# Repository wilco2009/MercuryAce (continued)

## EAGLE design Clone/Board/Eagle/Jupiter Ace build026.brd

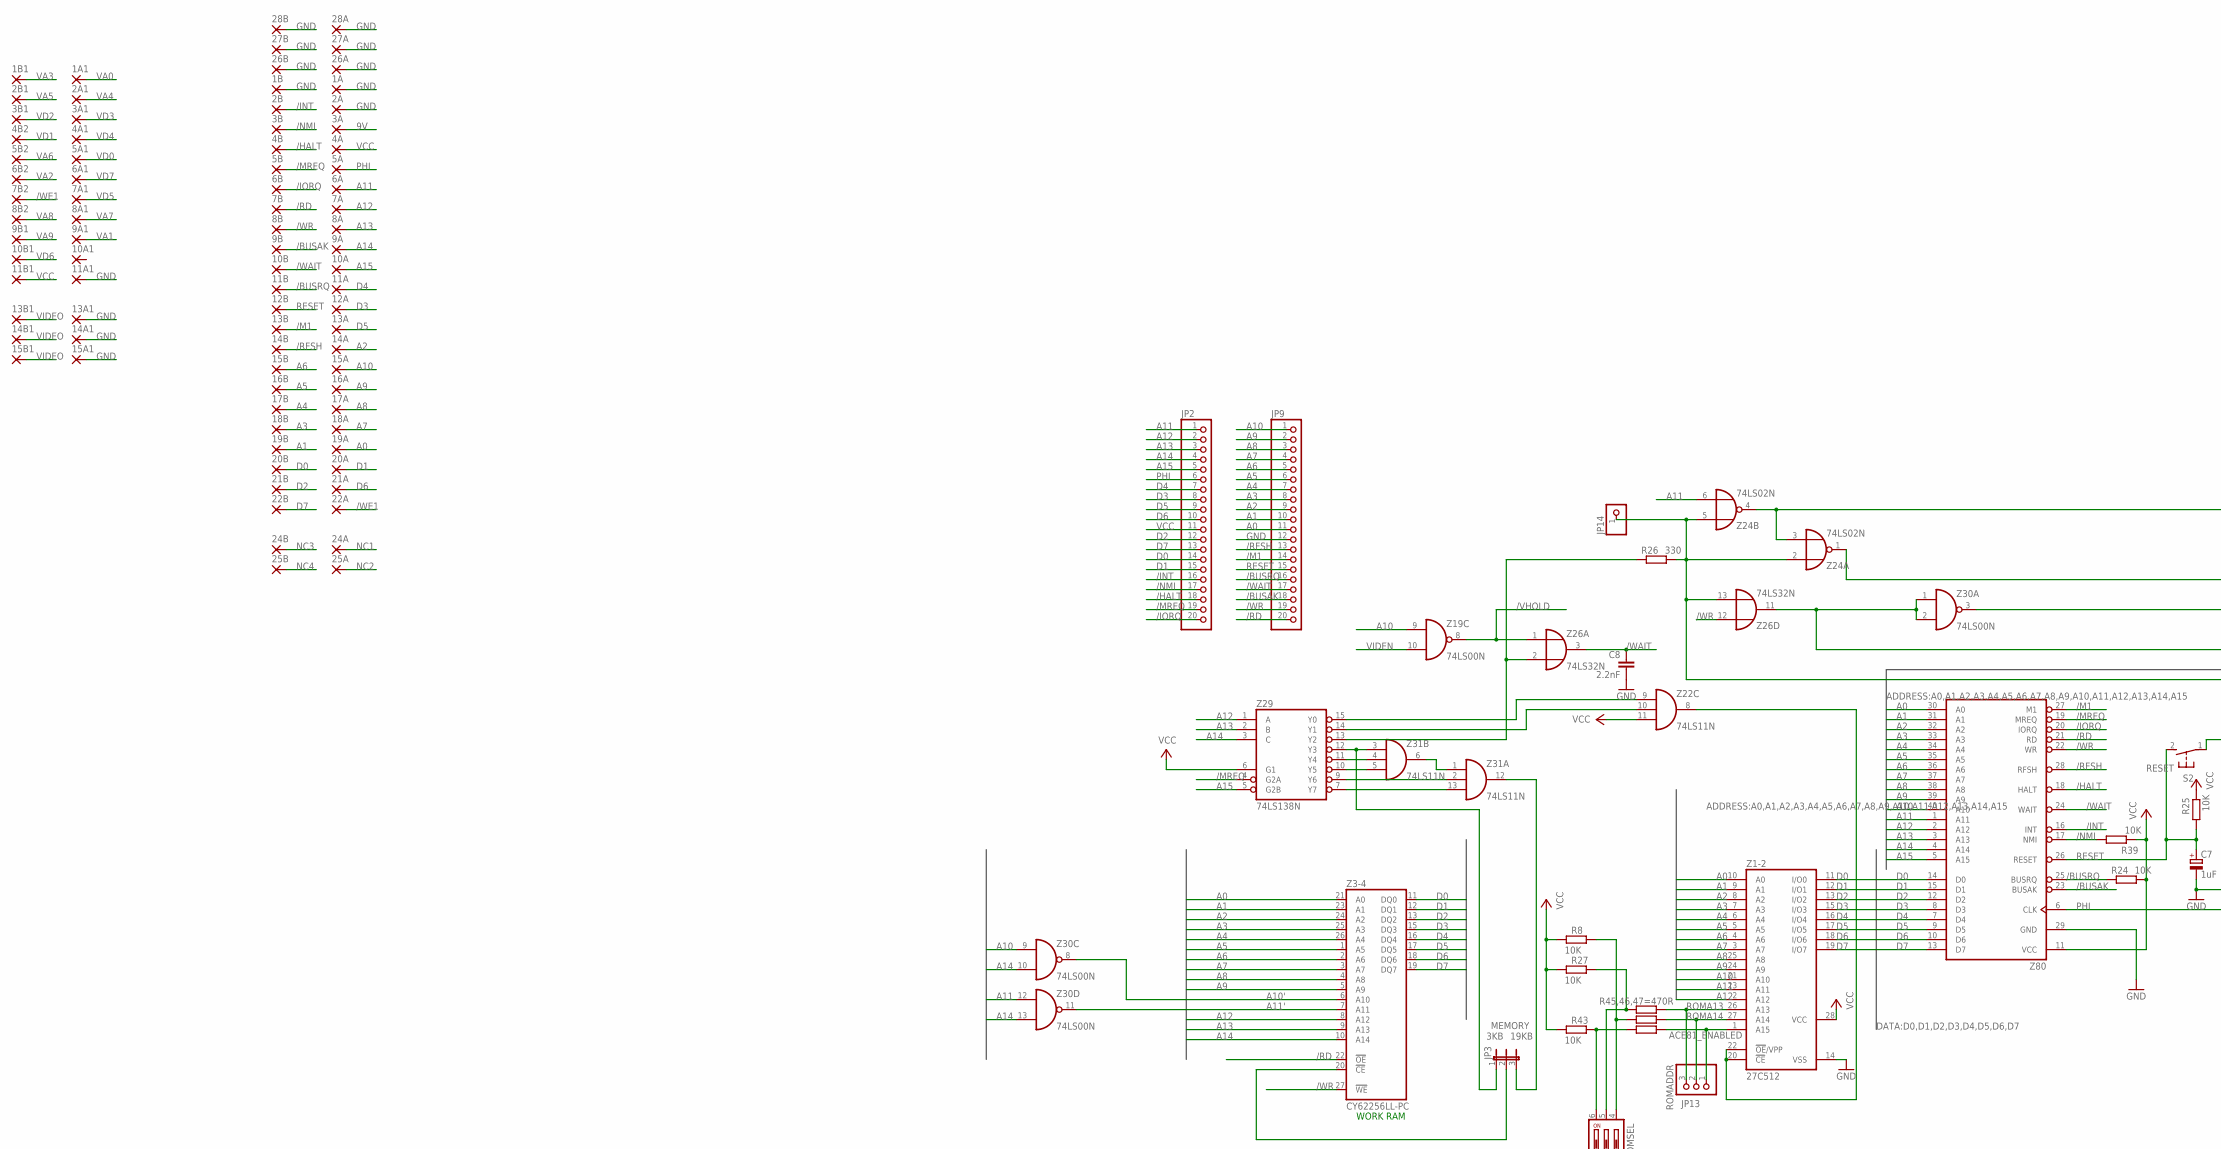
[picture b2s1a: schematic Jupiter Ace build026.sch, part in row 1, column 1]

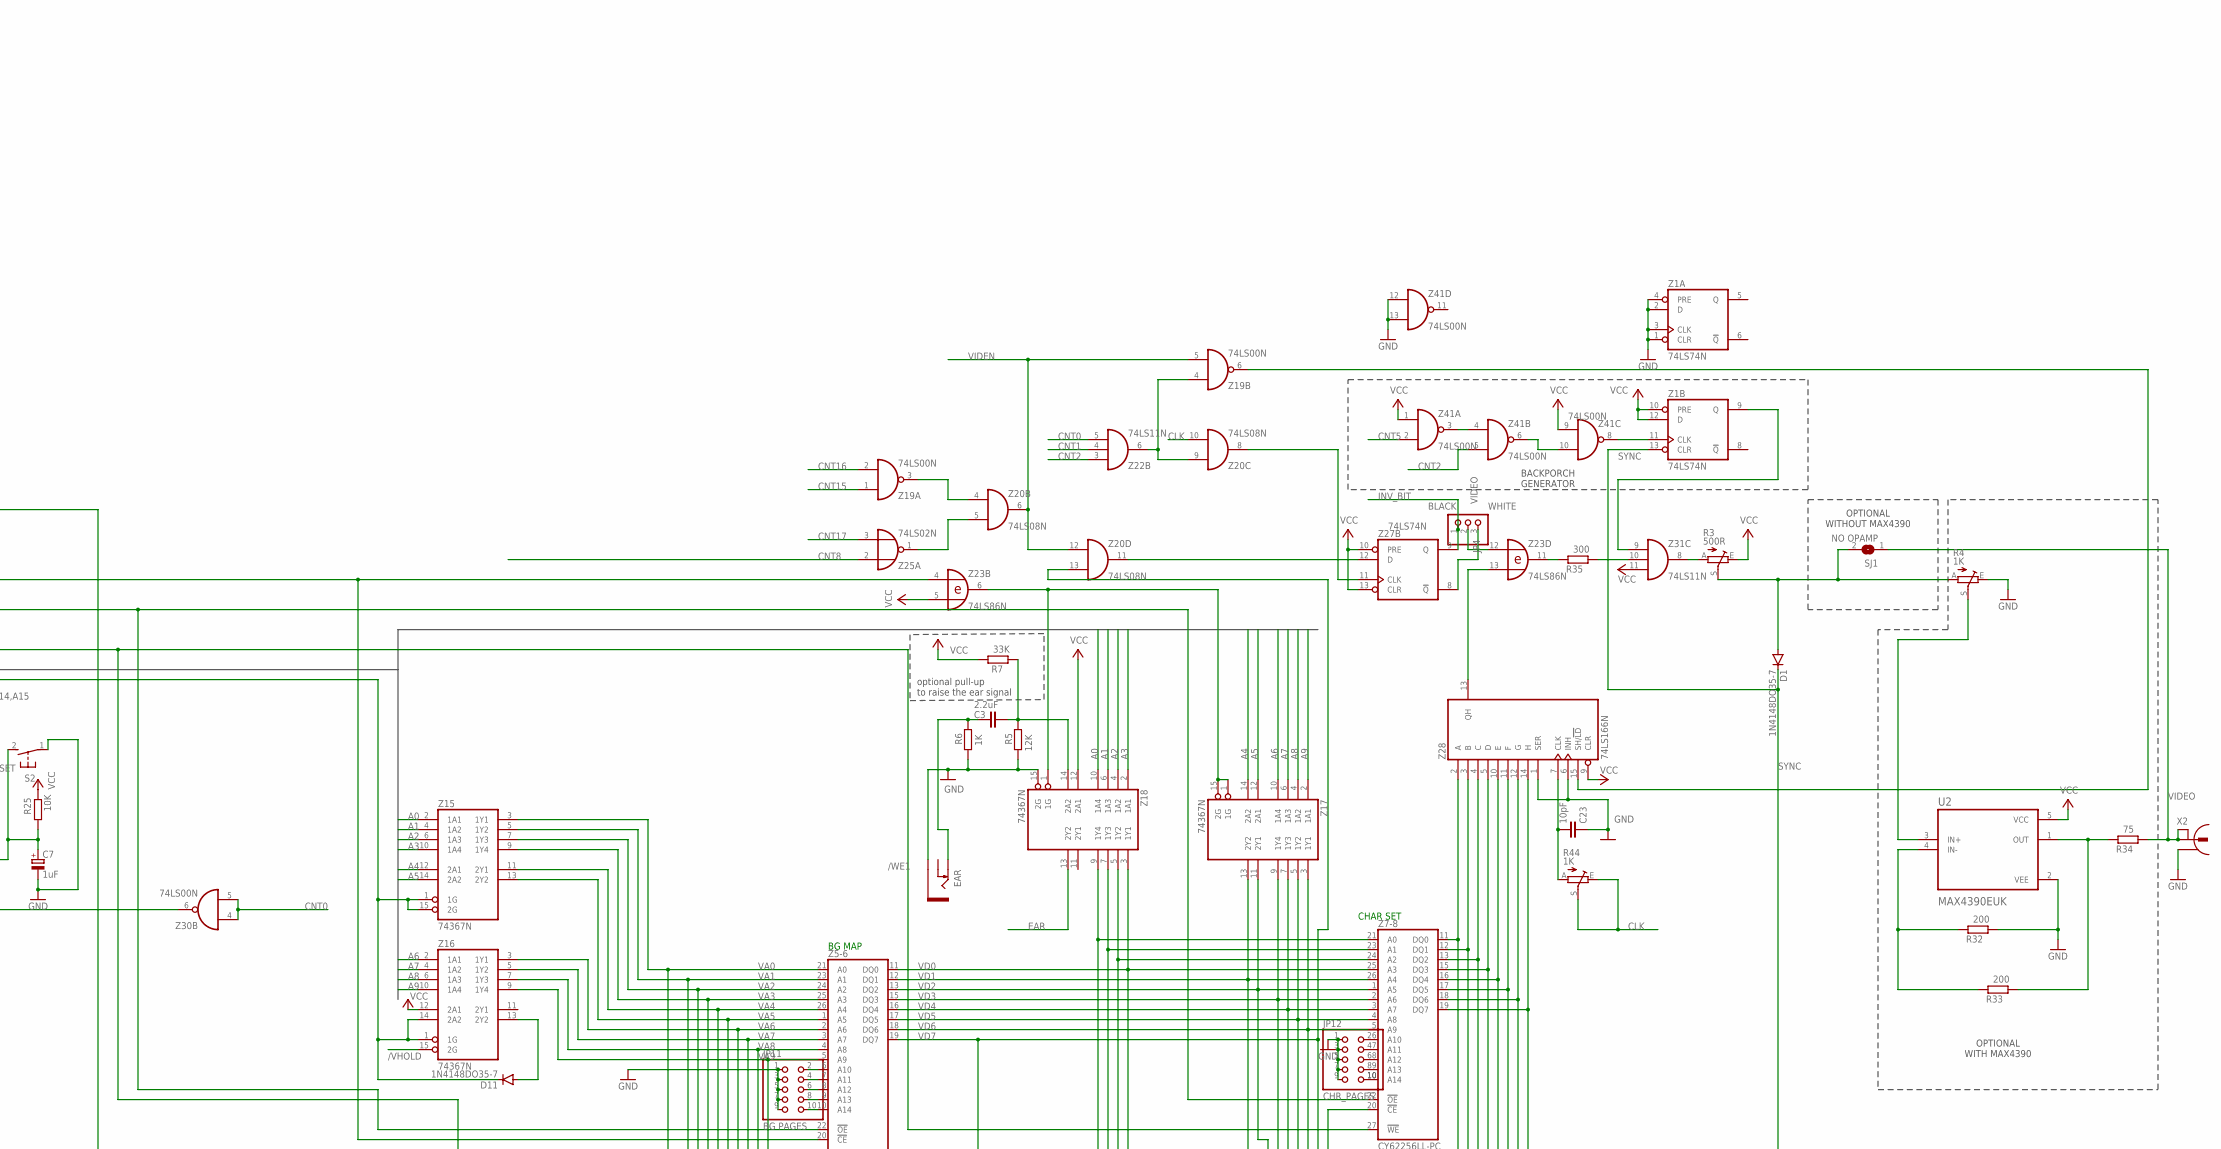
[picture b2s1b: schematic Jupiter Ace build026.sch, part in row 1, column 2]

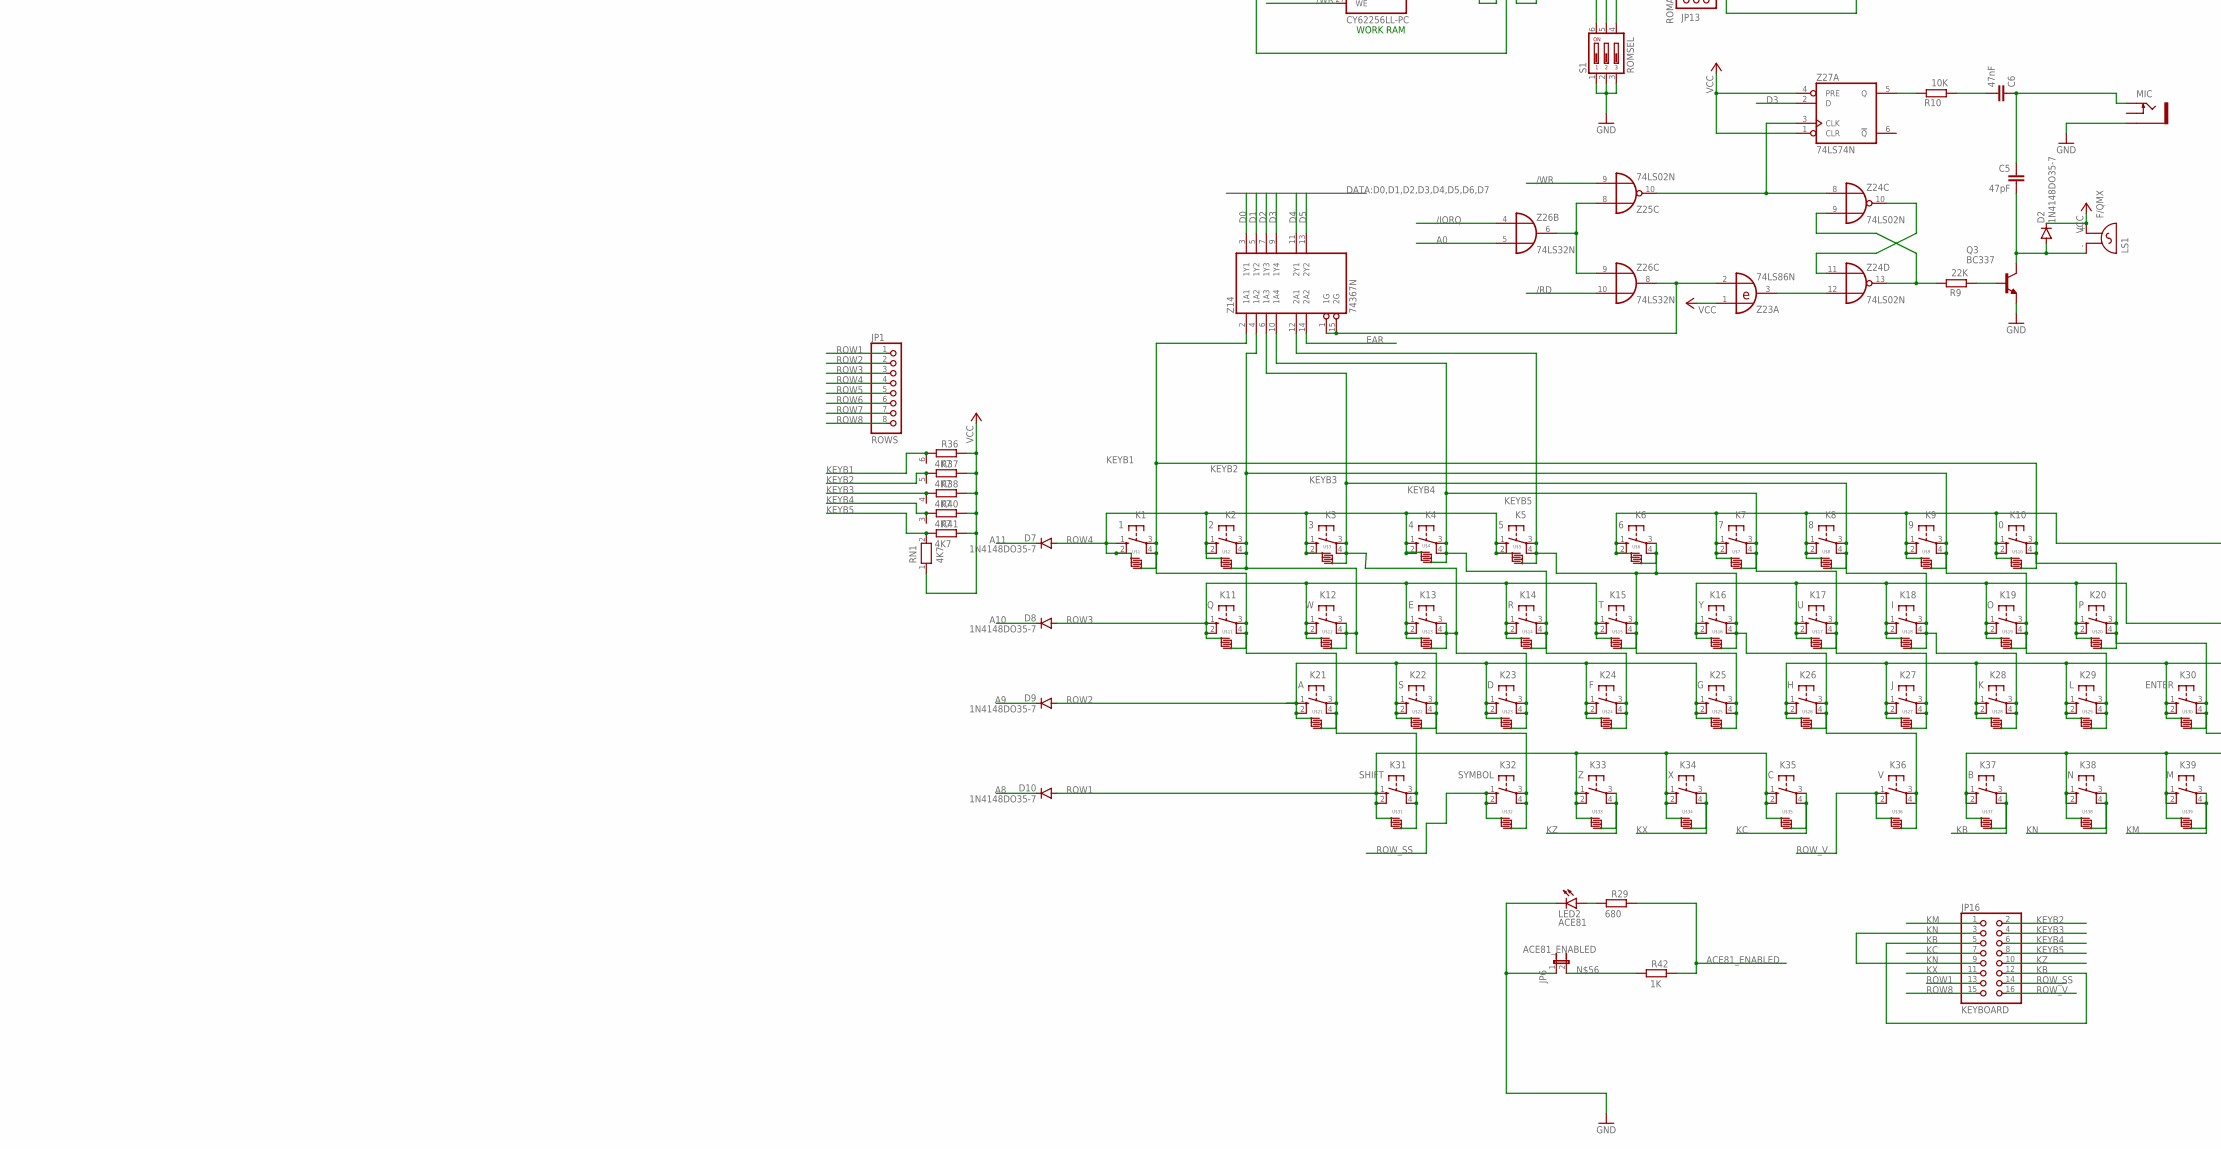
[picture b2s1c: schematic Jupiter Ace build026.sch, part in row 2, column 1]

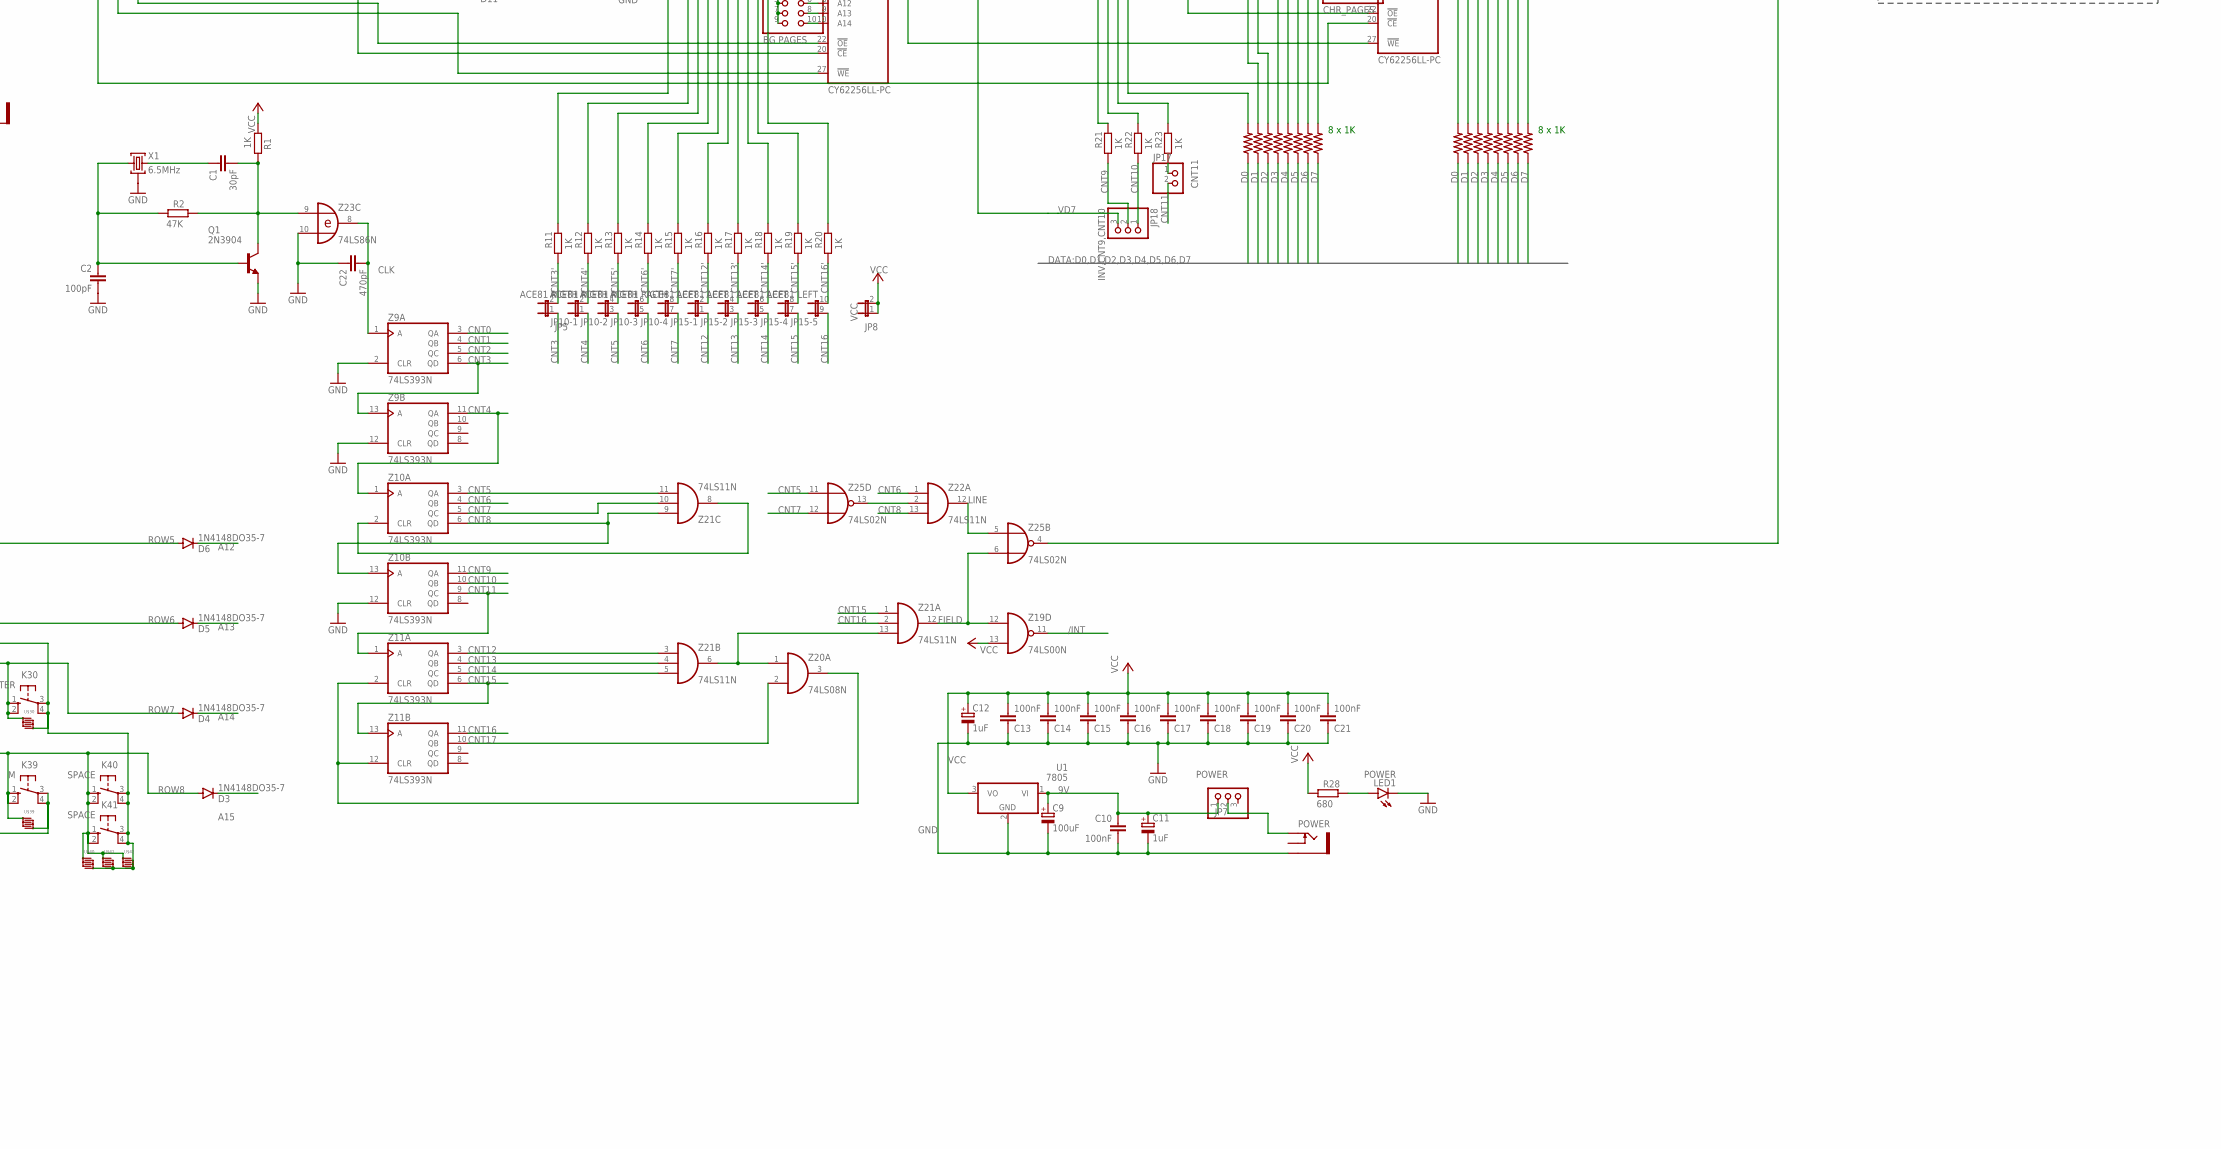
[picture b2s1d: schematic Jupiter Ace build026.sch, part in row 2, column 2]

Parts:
1A, 1A1, 1B, 1B1, 2A, 2A1, 2B, 2B1, 3A, 3A1, 3B, 3B1, 4A, 4A1, 4B, 4B2, 5A, 5A1, 5B, 5B2, 6A, 6A1, 6B, 6B2, 7A, 7A1, 7B, 7B2, 8A, 8A1, 8B, 8B2, 9A, 9A1, 9B, 9B1, 10A, 10A1, 10B, 10B1, 11A, 11A1, 11B, 11B1, 12A, 12B, 13A, 13A1, 13B, 13B1, 14A, 14A1, 14B, 14B1, 15A, 15A1, 15B, 15B1, 16A, 16B, 17A, 17B, 18A, 18B, 19A, 19B, 20A, 20B, 21A, 21B, 22A, 22B, 24A, 24B, 25A, 25B, 26A, 26B, 27A, 27B, 28A, 28B: SMD2EDGEPIN; EDGEPIN
C1: 30pF; C025-025X050
C2: 100pF; C025-025X050
C3: 2.2uF; C025-025X050
C5: 47pF; C025-025X050
C6: 47nF; C025-025X050
C7, C11, C12: 1uF; E1,8-4
C8: 2.2nF; C025-025X050
C9: 100uF; E1,8-4
C10, C13, C14, C15, C16, C17, C18, C19, C20, C21: 100nF; C025-025X050
C22: 470pF; C025-025X050
C23: 10pF; C025-025X050
D1, D2, D3, D4, D5, D6, D7, D8, D9, D10, D11: 1N4148DO35-7; DO35-7
EAR: PJ302M
JP1: ROWS; 1X08
JP2, JP9: PINHD-1X20; 1X20
JP3: MEMORY; JP2
JP4: VIDEO; 1X03
JP5: JP1E1Q; JP1Q
JP6: ACE81_ENABLED; JP1Q
JP7: POWER; 1X03
JP8: VCC; JP1Q
JP10: ACE81 RIGTH; JP4Q
JP11: BG PAGES; 2X05
JP12: CHR_PAGES; 2X05
JP13: ROMADDR; 1X03
JP14: PINHD-1X1; 1X01
JP15: ACE81 LEFT; JP5Q
JP16: KEYBOARD; 2X08
JP17: CNT11; 1X02
JP18: INV,CNT9,CNT10; 1X03
K1: 1; B3F-40XXNOHOLE
K2: 2; B3F-40XXNOHOLE
K3: 3; B3F-40XXNOHOLE
K4: 4; B3F-40XXNOHOLE
K5: 5; B3F-40XXNOHOLE
K6: 6; B3F-40XXNOHOLE
K7: 7; B3F-40XXNOHOLE
K8: 8; B3F-40XXNOHOLE
K9: 9; B3F-40XXNOHOLE
K10: 0; B3F-40XXNOHOLE
K11: Q; B3F-40XXNOHOLE
K12: W; B3F-40XXNOHOLE
K13: E; B3F-40XXNOHOLE
K14: R; B3F-40XXNOHOLE
K15: T; B3F-40XXNOHOLE
K16: Y; B3F-40XXNOHOLE
K17: U; B3F-40XXNOHOLE
K18: I; B3F-40XXNOHOLE
K19: O; B3F-40XXNOHOLE
K20: P; B3F-40XXNOHOLE
K21: A; B3F-40XXNOHOLE
K22: S; B3F-40XXNOHOLE
K23: D; B3F-40XXNOHOLE
K24: F; B3F-40XXNOHOLE
K25: G; B3F-40XXNOHOLE
K26: H; B3F-40XXNOHOLE
K27: J; B3F-40XXNOHOLE
K28: K; B3F-40XXNOHOLE
K29: L; B3F-40XXNOHOLE
K30: ENTER; B3F-40XXNOHOLE
K31: SHIFT; B3F-40XXNOHOLE
K32: SYMBOL; B3F-40XXNOHOLE
K33: Z; B3F-40XXNOHOLE
K34: X; B3F-40XXNOHOLE
K35: C; B3F-40XXNOHOLE
K36: V; B3F-40XXNOHOLE
K37: B; B3F-40XXNOHOLE
K38: N; B3F-40XXNOHOLE
K39: M; B3F-40XXNOHOLE
K40, K41: SPACE; B3F-40XXNOHOLE
LED1: POWER; LED3MM
LED2: ACE81; LED3MM
LS1: F/QMX
MIC: PJ302M
POWER: PJ302M
Q1: 2N3904; TO92
Q3: BC337; TO92
R1, R6, R11, R12, R13, R14, R15, R16, R17, R18, R19, R20, R42: 1K; 0204/7
R2: 47K; 0204/7
R3: 500R; B25P
R4, R44: 1K; B25P
R5: 12K; 0204/7
R7: 33K; 0204/7
R8, R10, R24, R25, R27, R39, R43: 10K; 0204/7
R9: 22K; 0204/7
R21, R22, R23, R100, R101, R102, R103, R104, R105, R106, R107, R200, R201, R202, R203, R204, R205, R206, R207: 1K; 0204V
R26: 330; 0204/7
R28, R29: 680; 0204/7
R32, R33: 200; 0204/7
R34: 75; 0204/7
R35: 300; 0204/7
R36, R37, R38, R40, R41: 4K7; 0207/10
R45, R46, R47: 470R; 0204/7
RN1: 4K7; RN-6
S1: ROMSEL; DP-03
S2: RESET; B3F-31XX
SJ1: NO OPAMP; SJ
U1: 7805; TO220V
U2: MAX4390EUK; SOT95P280X145-5N
U$1, U$2, U$3, U$4, U$5, U$6, U$7, U$8, U$9, U$10, U$11, U$12, U$13, U$14, U$15, U$16, U$17, U$18, U$19, U$20, U$21, U$22, U$23, U$24, U$25, U$26, U$27, U$28, U$29, U$30, U$31, U$32, U$33, U$34, U$35, U$36, U$37, U$38, U$39, U$40, U$41, U$42: 40-XX-CARBON; CARBONB3F
X1: 6.5MHz; HC49U
X2: CON-CONRAD_736880-49
Z0: Z80; DIL40
Z1, Z27: 74LS74N; DIL14
Z1-2: 27C512; DIL28-6
Z3-4, Z5-6, Z7-8: CY62256LL-PC; DIL28-6
Z9, Z10, Z11: 74LS393N; DIL14
Z14, Z15, Z16, Z17, Z18: 74367N; DIL16
Z19, Z30, Z41: 74LS00N; DIL14
Z20: 74LS08N; DIL14
Z21, Z22, Z31: 74LS11N; DIL14
Z23: 74LS86N; DIL14
Z24, Z25: 74LS02N; DIL14
Z26: 74LS32N; DIL14
Z28: 74LS166N; DIL16
Z29: 74LS138N; DIL16

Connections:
9V: 3A.1, C9.+, C10.1, C11.+, JP7.1, U1.1 (VI)
/BUSAK: 9B.1, JP9.18, Z0.23 (BUSAK)
/BUSRQ: 11B.1, JP9.16, R24.1, Z0.25 (BUSRQ)
/HALT: 4B.1, JP2.18, Z0.18 (HALT)
/INT: 2B.1, JP2.16, Z0.16 (INT), Z19.11 (O)
/IORQ: 6B.1, JP2.20, Z0.20 (IORQ), Z26.4 (I0)
/M1: 13B.1, JP9.14, Z0.27 (M1)
/MREQ: 5B.1, JP2.19, Z0.19 (MREQ), Z29.4 (G2A)
/NMI: 3B.1, JP2.17, R39.1, Z0.17 (NMI)
/RD: 7B.1, JP9.20, Z0.21 (RD), Z3-4.22 (!OE), Z26.10 (I1)
/RFSH: 14B.1, JP9.13, Z0.28 (RFSH)
/VHOLD: Z16.15 (2G), Z19.8 (O), Z26.1 (I0)
/WAIT: 10B.1, C8.1, JP9.17, Z0.24 (WAIT), Z26.3 (O)
/WE1: 7B2.1, 22A.1, Z5-6.27 (!WE), Z7-8.27 (!WE), Z26.11 (O), Z30.1 (I0), Z30.2 (I1)
/WR: 8B.1, JP9.19, Z0.22 (WR), Z3-4.27 (!WE), Z25.9 (I1), Z26.12 (I0)
A0: 19A.1, JP9.11, Z0.30 (A0), Z1-2.10 (A0), Z3-4.21 (A0), Z15.2 (1A1), Z18.10 (1A4), Z26.5 (I1)
A1: 19B.1, JP9.10, Z0.31 (A1), Z1-2.9 (A1), Z3-4.23 (A1), Z15.4 (1A2), Z18.6 (1A3)
A2: 14A.1, JP9.9, Z0.32 (A2), Z1-2.8 (A2), Z3-4.24 (A2), Z15.6 (1A3), Z18.4 (1A2)
A3: 18B.1, JP9.8, Z0.33 (A3), Z1-2.7 (A3), Z3-4.25 (A3), Z15.10 (1A4), Z18.2 (1A1)
A4: 17B.1, JP9.7, Z0.34 (A4), Z1-2.6 (A4), Z3-4.26 (A4), Z15.12 (2A1), Z17.14 (2A2)
A5: 16B.1, JP9.6, Z0.35 (A5), Z1-2.5 (A5), Z3-4.1 (A5), Z15.14 (2A2), Z17.12 (2A1)
A6: 15B.1, JP9.5, Z0.36 (A6), Z1-2.4 (A6), Z3-4.2 (A6), Z16.2 (1A1), Z17.10 (1A4)
A7: 18A.1, JP9.4, Z0.37 (A7), Z1-2.3 (A7), Z3-4.3 (A7), Z16.4 (1A2), Z17.6 (1A3)
A8: 17A.1, D10.C, JP9.3, Z0.38 (A8), Z1-2.25 (A8), Z3-4.4 (A8), Z16.6 (1A3), Z17.4 (1A2)
A9: 16A.1, D9.C, JP9.2, Z0.39 (A9), Z1-2.24 (A9), Z3-4.5 (A9), Z16.10 (1A4), Z17.2 (1A1)
A10: 15A.1, D8.C, JP9.1, Z0.40 (A10), Z1-2.21 (A10), Z19.9 (I0), Z30.9 (I0)
A10': Z3-4.6 (A10), Z30.8 (O)
A11: 6A.1, D7.C, JP2.1, Z0.1 (A11), Z1-2.23 (A11), Z24.6 (I1), Z30.12 (I0)
A11': Z3-4.7 (A11), Z30.11 (O)
A12: 7A.1, D6.C, JP2.2, Z0.2 (A12), Z1-2.2 (A12), Z3-4.8 (A12), Z29.1 (A)
A13: 8A.1, D5.C, JP2.3, Z0.3 (A13), Z3-4.9 (A13), Z29.2 (B)
A14: 9A.1, D4.C, JP2.4, Z0.4 (A14), Z3-4.10 (A14), Z29.3 (C), Z30.10 (I1), Z30.13 (I1)
A15: 10A.1, D3.C, JP2.5, Z0.5 (A15), Z29.5 (G2B)
ACE81_ENABLED: JP13.1, R29.2, R42.2, R47.2, Z1-2.1 (A15)
AMPLIF_IN: R4.S, U2.3 (IN+)
AMPLIF_OUT: R33.1, R34.2, U2.1 (OUT)
CLK: C22.2, R44.E, R44.S, Z9.1 (A), Z20.10 (I1), Z23.8 (O)
CNT0: Z9.3 (QA), Z22.5 (I2), Z30.4 (I0), Z30.5 (I1)
CNT1: Z9.4 (QB), Z22.4 (I1)
CNT2: Z9.5 (QC), Z22.3 (I0), Z41.5 (I1)
CNT3: JP5.1, Z9.6 (QD), Z9.13 (A)
CNT3': JP5.2, R11.1
CNT4: JP10.1, Z9.11 (QA), Z10.1 (A)
CNT4': JP10.2, R12.1
CNT5: JP10.3 (1), Z10.3 (QA), Z21.11 (I2), Z25.11 (I0), Z41.2 (I1)
CNT5': JP10.4 (2), R13.1
CNT6: JP10.5 (1), Z10.4 (QB), Z22.1 (I0)
CNT6': JP10.6 (2), R14.1
CNT7: JP10.7 (1), Z10.5 (QC), Z21.10 (I1), Z25.12 (I1)
CNT7': JP10.8 (2), R15.1
CNT8: Z10.6 (QD), Z10.13 (A), Z21.9 (I0), Z22.13 (I2), Z25.2 (I0)
CNT9: JP18.2, R21.1, Z10.11 (QA)
CNT10: JP18.1, R22.1, Z10.10 (QB)
CNT11: JP17.2, Z10.9 (QC), Z11.1 (A)
CNT12: JP15.1, Z11.3 (QA), Z21.3 (I0)
CNT12': JP15.2, R16.1
CNT13: JP15.3 (1), Z11.4 (QB), Z21.4 (I1)
CNT13': JP15.4 (2), R17.1
CNT14: JP15.5 (1), Z11.5 (QC), Z21.5 (I2)
CNT14': JP15.6 (2), R18.1
CNT15: JP15.7 (1), Z11.6 (QD), Z11.13 (A), Z19.1 (I0), Z21.1 (I0)
CNT15': JP15.8 (2), R19.1
CNT16: JP15.9 (1), Z11.11 (QA), Z19.2 (I1), Z21.2 (I1)
CNT16': JP15.10 (2), R20.1
CNT17: Z11.10 (QB), Z20.2 (I1), Z25.3 (I1)
D0: 20B.1, JP2.14, R100.1, R200.1, Z0.14 (D0), Z1-2.11 (I/O0), Z3-4.11 (DQ0), Z14.3 (1Y1)
D1: 20A.1, JP2.15, R101.1, R201.1, Z0.15 (D1), Z1-2.12 (I/O1), Z3-4.12 (DQ1), Z14.5 (1Y2)
D2: 21B.1, JP2.12, R102.1, R202.1, Z0.12 (D2), Z1-2.13 (I/O2), Z3-4.13 (DQ2), Z14.7 (1Y3)
D3: 12A.1, JP2.8, R103.1, R203.1, Z0.8 (D3), Z1-2.15 (I/O3), Z3-4.15 (DQ3), Z14.9 (1Y4), Z27.2 (D)
D4: 11A.1, JP2.7, R104.1, R204.1, Z0.7 (D4), Z1-2.16 (I/O4), Z3-4.16 (DQ4), Z14.11 (2Y1)
D5: 13A.1, JP2.9, R105.1, R205.1, Z0.9 (D5), Z1-2.17 (I/O5), Z3-4.17 (DQ5), Z14.13 (2Y2)
D6: 21A.1, JP2.10, R106.1, R206.1, Z0.10 (D6), Z1-2.18 (I/O6), Z3-4.18 (DQ6)
D7: 22B.1, JP2.13, R107.1, R207.1, Z0.13 (D7), Z1-2.19 (I/O7), Z3-4.19 (DQ7)
EAR: Z14.14 (2A2), Z18.13 (2Y2)
FIELD: Z19.12 (I0), Z21.12 (O), Z25.6 (I1)
GND: 1A.1, 1B.1, 2A.1, 11A1.1, 13A1.1, 14A1.1, 15A1.1, 26A.1, 26B.1, 27A.1, 27B.1, 28A.1, 28B.1, C2.2, C7.-, C8.2, C9.-, C10.2, C11.-, C12.-, C13.1, C14.1, C15.1, C16.1, C17.1, C18.1, C19.1, C20.1, C21.1, C22.1, C23.1, EAR.GND (SLEEVE), JP6.1, JP9.12, JP11.1, JP11.3, JP11.5, JP11.7, JP11.9, JP12.1, JP12.3, JP12.5, JP12.7, JP12.9, LED1.K (C), LED2.K (C), MIC.GND (SLEEVE), POWER.GND (SLEEVE), Q1.3 (E), Q3.1 (E), R4.E, R5.1, R6.1, R32.1, S1.1, S1.2, S1.3, S2.1, U1.2 (GND), U2.2 (VEE), X1.2, X2.1 (2), Z0.29 (GND), Z1.1 (CLR), Z1.2 (D), Z1.3 (CLK), Z1.4 (PRE), Z1.7 (GND), Z1-2.14 (VSS), Z3-4.14 (GND), Z5-6.14 (GND), Z7-8.14 (GND), Z9.2 (CLR), Z9.7 (GND), Z9.12 (CLR), Z10.7 (GND), Z10.12 (CLR), Z11.7 (GND), Z14.8 (GND), Z15.8 (GND), Z16.8 (GND), Z17.8 (GND), Z18.8 (GND), Z18.15 (2G), Z19.7 (GND), Z20.7 (GND), Z21.7 (GND), Z22.7 (GND), Z23.7 (GND), Z23.10 (I1), Z24.7 (GND), Z25.7 (GND), Z26.7 (GND), Z27.7 (GND), Z28.1 (SER), Z28.6 (INH), Z28.8 (GND), Z29.8 (GND), Z30.7 (GND), Z31.7 (GND), Z41.7 (GND), Z41.12 (I0), Z41.13 (I1)
INV_BIT: JP4.1, Z27.9 (Q)
KB: JP16.5, JP16.12, K37.3, K37.4 (P1), U$37.P$2 (2)
KC: JP16.7, K35.3, K35.4 (P1), U$35.P$2 (2)
KEYB1: K1.3, K1.4 (P1), K10.3, K10.4 (P1), K11.3, K11.4 (P1), K20.3, K20.4 (P1), K21.3, K21.4 (P1), K30.3, K30.4 (P1), K31.3, K31.4 (P1), K40.3, K40.4 (P1), K41.3, K41.4 (P1), R36.1, RN1.6, U$1.P$2 (2), U$10.P$2 (2), U$11.P$2 (2), U$20.P$2 (2), U$21.P$2 (2), U$30.P$2 (2), U$31.P$2 (2), U$40.P$2 (2), U$41.P$2 (2), U$42.P$2 (2), Z14.2 (1A1)
KEYB2: JP16.2, K2.3, K2.4 (P1), K9.3, K9.4 (P1), K12.3, K12.4 (P1), K19.3, K19.4 (P1), K22.3, K22.4 (P1), K29.3, K29.4 (P1), K32.3, K32.4 (P1), R37.1, RN1.5, U$2.P$2 (2), U$9.P$2 (2), U$12.P$2 (2), U$19.P$2 (2), U$22.P$2 (2), U$29.P$2 (2), U$32.P$2 (2), Z14.4 (1A2)
KEYB3: JP16.4, K3.3, K3.4 (P1), K8.3, K8.4 (P1), K13.3, K13.4 (P1), K18.3, K18.4 (P1), K23.3, K23.4 (P1), K28.3, K28.4 (P1), R38.1, RN1.4, U$3.P$2 (2), U$8.P$2 (2), U$13.P$2 (2), U$18.P$2 (2), U$23.P$2 (2), U$28.P$2 (2), Z14.6 (1A3)
KEYB4: JP16.6, K4.3, K4.4 (P1), K7.3, K7.4 (P1), K14.3, K14.4 (P1), K17.3, K17.4 (P1), K24.3, K24.4 (P1), K27.3, K27.4 (P1), R40.1, RN1.3, U$4.P$2 (2), U$7.P$2 (2), U$14.P$2 (2), U$17.P$2 (2), U$24.P$2 (2), U$27.P$2 (2), Z14.10 (1A4)
KEYB5: JP16.8, K5.3, K5.4 (P1), K6.3, K6.4 (P1), K15.3, K15.4 (P1), K16.3, K16.4 (P1), K25.3, K25.4 (P1), K26.3, K26.4 (P1), K36.3, K36.4 (P1), R41.1, RN1.2, U$5.P$2 (2), U$6.P$2 (2), U$15.P$2 (2), U$16.P$2 (2), U$25.P$2 (2), U$26.P$2 (2), U$36.P$2 (2), Z14.12 (2A1)
KM: JP16.1, K39.3, K39.4 (P1), U$39.P$2 (2)
KN: JP16.3, JP16.9, K38.3, K38.4 (P1), U$38.P$2 (2)
KX: JP16.11, K34.3, K34.4 (P1), U$34.P$2 (2)
KZ: JP16.10, K33.3, K33.4 (P1), U$33.P$2 (2)
LINE: Z22.12 (O), Z25.5 (I0)
unnamed: Z1-2.20 (!CE), Z1-2.22 (!OE!/VPP), Z22.8 (O)
unnamed: R32.2, R33.2, U2.4 (IN-)
unnamed: Z41.3 (O), Z41.4 (I0)
unnamed: Z22.10 (I1), Z29.14 (Y1)
unnamed: Z22.9 (I0), Z29.15 (Y0)
unnamed: R26.1, Z26.2 (I1), Z29.13 (Y2)
unnamed: Z7-8.20 (!CE), Z24.3 (I1), Z24.4 (O)
unnamed: Z14.1 (1G), Z14.15 (2G), Z23.2 (I1), Z26.8 (O)
unnamed: JP3.1, Z29.12 (Y3), Z31.3 (I0)
unnamed: Z19.3 (O), Z20.4 (I0)
unnamed: Z20.5 (I1), Z25.1 (O)
unnamed: Z19.4 (I0), Z20.9 (I0), Z22.6 (O)
unnamed: Z20.11 (O), Z27.12 (D)
unnamed: Z20.8 (O), Z27.11 (CLK)
unnamed: D1.A, R3.S, R4.A, SJ1.2
unnamed: Z23.13 (I1), Z28.13 (QH)
unnamed: Z19.6 (O), Z28.15 (SH/!LD)
unnamed: R200.2, Z7-8.11 (DQ0), Z28.2 (A)
unnamed: R201.2, Z7-8.12 (DQ1), Z28.3 (B)
unnamed: R202.2, Z7-8.13 (DQ2), Z28.4 (C)
unnamed: R203.2, Z7-8.15 (DQ3), Z28.5 (D)
unnamed: R204.2, Z7-8.16 (DQ4), Z28.10 (E)
unnamed: R205.2, Z7-8.17 (DQ5), Z28.11 (F)
unnamed: R206.2, Z7-8.18 (DQ6), Z28.12 (G)
unnamed: R207.2, Z7-8.19 (DQ7), Z28.14 (H)
unnamed: Z17.1 (1G), Z17.15 (2G), Z18.1 (1G), Z23.6 (O)
unnamed: C3.2, R5.2, R7.1, Z18.14 (2A2)
unnamed: C3.1, EAR.TIP, R6.2
unnamed: Z5-6.20 (!CE), Z23.4 (I0), Z24.1 (O)
unnamed: Z5-6.22 (!OE), Z7-8.22 (!OE), Z30.3 (O)
unnamed: C23.2, R44.A, Z28.7 (CLK)
unnamed: Z41.6 (O), Z41.10 (I1)
unnamed: Z1.11 (CLK), Z41.8 (O)
unnamed: Z29.11 (Y4), Z31.4 (I1)
unnamed: R35.2, Z23.11 (O)
unnamed: JP3.2, Z3-4.20 (!CE)
unnamed: Z29.10 (Y5), Z31.5 (I2)
unnamed: Z29.9 (Y6), Z31.2 (I1)
unnamed: Z29.7 (Y7), Z31.13 (I2)
unnamed: Z31.1 (I0), Z31.6 (O)
unnamed: JP3.3, Z31.12 (O)
unnamed: JP4.3, Z27.8 (!Q)
unnamed: JP4.2, Z23.12 (I0)
unnamed: R8.2, R46.1, S1.4
unnamed: R27.2, R45.1, S1.5
unnamed: Z25.8 (I0), Z26.6 (O), Z26.9 (I0)
unnamed: R43.2, R47.1, S1.6
unnamed: JP6.2, R42.1
unnamed: JP11.8, Z5-6.9 (A13)
unnamed: D11.A, Z16.13 (2Y2)
unnamed: D11.C, JP14.1, R26.2, Z15.1 (1G), Z15.15 (2G), Z16.1 (1G), Z16.14 (2A2), Z24.2 (I0), Z24.5 (I0), Z26.13 (I1)
unnamed: Z23.3 (O), Z24.12 (I1)
unnamed: Z24.8 (I0), Z25.10 (O), Z27.3 (CLK)
unnamed: JP11.4, Z5-6.7 (A11)
unnamed: Z24.10 (O), Z24.11 (I0)
unnamed: R9.2, Z24.9 (I1), Z24.13 (O)
unnamed: Q3.2 (B), R9.1
unnamed: JP11.2, Z5-6.6 (A10)
unnamed: JP11.6, Z5-6.8 (A12)
unnamed: JP11.10, Z5-6.10 (A14)
unnamed: JP12.8, Z7-8.9 (A13)
unnamed: R10.2, Z27.5 (Q)
unnamed: JP12.2, Z7-8.6 (A10)
unnamed: C6.2, R10.1
unnamed: C5.1, C6.1, MIC.TIP
unnamed: C5.2, D2.A, LS1.- (1), Q3.3 (C)
unnamed: C1.2, Q1.1 (C), R1.2, R2.2, Z23.9 (I0)
unnamed: C1.1, X1.3
unnamed: C2.1, Q1.2 (B), R2.1, X1.1
unnamed: Z20.1 (I0), Z21.6 (O), Z21.13 (I2)
unnamed: Z11.2 (CLR), Z11.12 (CLR), Z20.3 (O)
unnamed: Z10.2 (CLR), Z21.8 (O)
unnamed: JP12.4, Z7-8.7 (A11)
unnamed: Z22.2 (I1), Z25.13 (O)
unnamed: JP12.6, Z7-8.8 (A12)
unnamed: JP12.10, Z7-8.10 (A14)
unnamed: Z1.9 (Q), Z31.9 (I0)
unnamed: JP17.1, R23.1
unnamed: R35.1, Z31.10 (I1)
unnamed: LED1.A, R28.2
unnamed: LED2.A, R29.1
unnamed: JP7.2, POWER.TIP
unnamed: R3.A, Z31.8 (O)
NC1: 24A.1
NC2: 25A.1
NC3: 24B.1
NC4: 25B.1
PHI: 5A.1, JP2.6, Z0.6 (CLK), Z30.6 (O)
RESET: 12B.1, C7.+, JP9.15, R25.1, S2.2 (S), Z0.26 (RESET)
ROMA13: JP13.3, R45.2, Z1-2.26 (A13)
ROMA14: JP13.2, R46.2, Z1-2.27 (A14)
ROW1: D10.A, JP1.1, JP16.13, K31.1 (S), K31.2 (S1), K33.1 (S), K33.2 (S1), K34.1 (S), K34.2 (S1), K35.1 (S), K35.2 (S1), U$31.P$1 (1), U$33.P$1 (1), U$34.P$1 (1), U$35.P$1 (1)
ROW2: D9.A, JP1.2, K21.1 (S), K21.2 (S1), K22.1 (S), K22.2 (S1), K23.1 (S), K23.2 (S1), K24.1 (S), K24.2 (S1), K25.1 (S), K25.2 (S1), U$21.P$1 (1), U$22.P$1 (1), U$23.P$1 (1), U$24.P$1 (1), U$25.P$1 (1)
ROW3: D8.A, JP1.3, K11.1 (S), K11.2 (S1), K12.1 (S), K12.2 (S1), K13.1 (S), K13.2 (S1), K14.1 (S), K14.2 (S1), K15.1 (S), K15.2 (S1), U$11.P$1 (1), U$12.P$1 (1), U$13.P$1 (1), U$14.P$1 (1), U$15.P$1 (1)
ROW4: D7.A, JP1.4, K1.1 (S), K1.2 (S1), K2.1 (S), K2.2 (S1), K3.1 (S), K3.2 (S1), K4.1 (S), K4.2 (S1), K5.1 (S), K5.2 (S1), U$1.P$1 (1), U$2.P$1 (1), U$3.P$1 (1), U$4.P$1 (1), U$5.P$1 (1)
ROW5: D6.A, JP1.5, K6.1 (S), K6.2 (S1), K7.1 (S), K7.2 (S1), K8.1 (S), K8.2 (S1), K9.1 (S), K9.2 (S1), K10.1 (S), K10.2 (S1), U$6.P$1 (1), U$7.P$1 (1), U$8.P$1 (1), U$9.P$1 (1), U$10.P$1 (1)
ROW6: D5.A, JP1.6, K16.1 (S), K16.2 (S1), K17.1 (S), K17.2 (S1), K18.1 (S), K18.2 (S1), K19.1 (S), K19.2 (S1), K20.1 (S), K20.2 (S1), U$16.P$1 (1), U$17.P$1 (1), U$18.P$1 (1), U$19.P$1 (1), U$20.P$1 (1)
ROW7: D4.A, JP1.7, K26.1 (S), K26.2 (S1), K27.1 (S), K27.2 (S1), K28.1 (S), K28.2 (S1), K29.1 (S), K29.2 (S1), K30.1 (S), K30.2 (S1), U$26.P$1 (1), U$27.P$1 (1), U$28.P$1 (1), U$29.P$1 (1), U$30.P$1 (1)
ROW8: D3.A, JP1.8, JP16.15, K37.1 (S), K37.2 (S1), K38.1 (S), K38.2 (S1), K39.1 (S), K39.2 (S1), K40.1 (S), K40.2 (S1), K41.1 (S), K41.2 (S1), U$37.P$1 (1), U$38.P$1 (1), U$39.P$1 (1), U$40.P$1 (1), U$41.P$1 (1), U$42.P$1 (1)
ROW_SS: JP16.14, K32.1 (S), K32.2 (S1), U$32.P$1 (1)
ROW_V: JP16.16, K36.1 (S), K36.2 (S1), U$36.P$1 (1)
S0000: R21.2, Z7-8.21 (A0), Z18.9 (1Y4)
S0001: R22.2, Z7-8.23 (A1), Z18.7 (1Y3)
S0002: R23.2, Z7-8.24 (A2), Z18.5 (1Y2)
SYNC: D1.C, Z1.13 (CLR), Z25.4 (O)
VA0: 1A1.1, R11.2, Z5-6.21 (A0), Z15.3 (1Y1)
VA1: 9A1.1, R12.2, Z5-6.23 (A1), Z15.5 (1Y2)
VA2: 6B2.1, R13.2, Z5-6.24 (A2), Z15.7 (1Y3)
VA3: 1B1.1, R14.2, Z5-6.25 (A3), Z15.9 (1Y4)
VA4: 2A1.1, R15.2, Z5-6.26 (A4), Z15.11 (2Y1)
VA5: 2B1.1, R16.2, Z5-6.1 (A5), Z15.13 (2Y2)
VA6: 5B2.1, R17.2, Z5-6.2 (A6), Z16.3 (1Y1)
VA7: 8A1.1, R18.2, Z5-6.3 (A7), Z16.5 (1Y2)
VA8: 8B2.1, R19.2, Z5-6.4 (A8), Z16.7 (1Y3)
VA9: 9B1.1, R20.2, Z5-6.5 (A9), Z16.9 (1Y4)
VCC: 4A.1, 11B1.1, C12.+, C13.2, C14.2, C15.2, C16.2, C17.2, C18.2, C19.2, C20.2, C21.2, D2.C, JP2.11, JP8.1, JP8.2, LS1.+ (2), R1.1, R3.E, R7.2, R8.1, R24.2, R25.2, R27.1, R28.1, R36.2, R37.2, R38.2, R39.2, R40.2, R41.2, R43.1, RN1.1, U1.3 (VO), U2.5 (VCC), Z0.11 (VCC), Z1.10 (PRE), Z1.12 (D), Z1.14 (VCC), Z1-2.28 (VCC), Z3-4.28 (VCC), Z5-6.28 (VCC), Z7-8.28 (VCC), Z9.14 (VCC), Z10.14 (VCC), Z11.14 (VCC), Z14.16 (VCC), Z15.16 (VCC), Z16.12 (2A1), Z16.16 (VCC), Z17.16 (VCC), Z18.12 (2A1), Z18.16 (VCC), Z19.13 (I1), Z19.14 (VCC), Z20.14 (VCC), Z21.14 (VCC), Z22.11 (I2), Z22.14 (VCC), Z23.1 (I0), Z23.5 (I1), Z23.14 (VCC), Z24.14 (VCC), Z25.14 (VCC), Z26.14 (VCC), Z27.1 (CLR), Z27.4 (PRE), Z27.10 (PRE), Z27.13 (CLR), Z27.14 (VCC), Z28.9 (CLR), Z28.16 (VCC), Z29.6 (G1), Z29.16 (VCC), Z30.14 (VCC), Z31.11 (I2), Z31.14 (VCC), Z41.1 (I0), Z41.9 (I0), Z41.14 (VCC)
VD0: 5A1.1, R100.2, Z5-6.11 (DQ0), Z7-8.25 (A3), Z18.3 (1Y1)
VD1: 4B2.1, R101.2, Z5-6.12 (DQ1), Z7-8.26 (A4), Z17.13 (2Y2)
VD2: 3B1.1, R102.2, Z5-6.13 (DQ2), Z7-8.1 (A5), Z17.11 (2Y1)
VD3: 3A1.1, R103.2, Z5-6.15 (DQ3), Z7-8.2 (A6), Z17.9 (1Y4)
VD4: 4A1.1, R104.2, Z5-6.16 (DQ4), Z7-8.3 (A7), Z17.7 (1Y3)
VD5: 7A1.1, R105.2, Z5-6.17 (DQ5), Z7-8.4 (A8), Z17.5 (1Y2)
VD6: 10B1.1, R106.2, Z5-6.18 (DQ6), Z7-8.5 (A9), Z17.3 (1Y1)
VD7: 6A1.1, JP18.3, R107.2, Z5-6.19 (DQ7), Z20.13 (I1)
VIDEN: Z19.5 (I1), Z19.10 (I1), Z20.6 (O), Z20.12 (I0)
VIDEO: 13B1.1, 14B1.1, 15B1.1, R34.1, SJ1.1, X2.2 (1), X2.2@2 (2)

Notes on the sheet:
8 x 1K
WORK RAM
BG MAP
CHAR SET
19KB
3KB
BLACK
WHITE
OPTIONAL WITHOUT MAX4390
BACKPORCH GENERATOR
R45,46,47=470R
OPTIONAL WITH MAX4390
optional pull-up to raise the ear signal
